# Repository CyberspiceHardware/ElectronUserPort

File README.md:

# Acorn Electron User Port Cartridge 

This is a BBC micro compatible user port cartridge which can be configured
to sit at any of the 16 byte addresses spaces 0xFC80 and above. The standard
address is 0xFCB0.

It also supports a ROM/RAM/FLASH device which can be a 16KB or 32KB part.

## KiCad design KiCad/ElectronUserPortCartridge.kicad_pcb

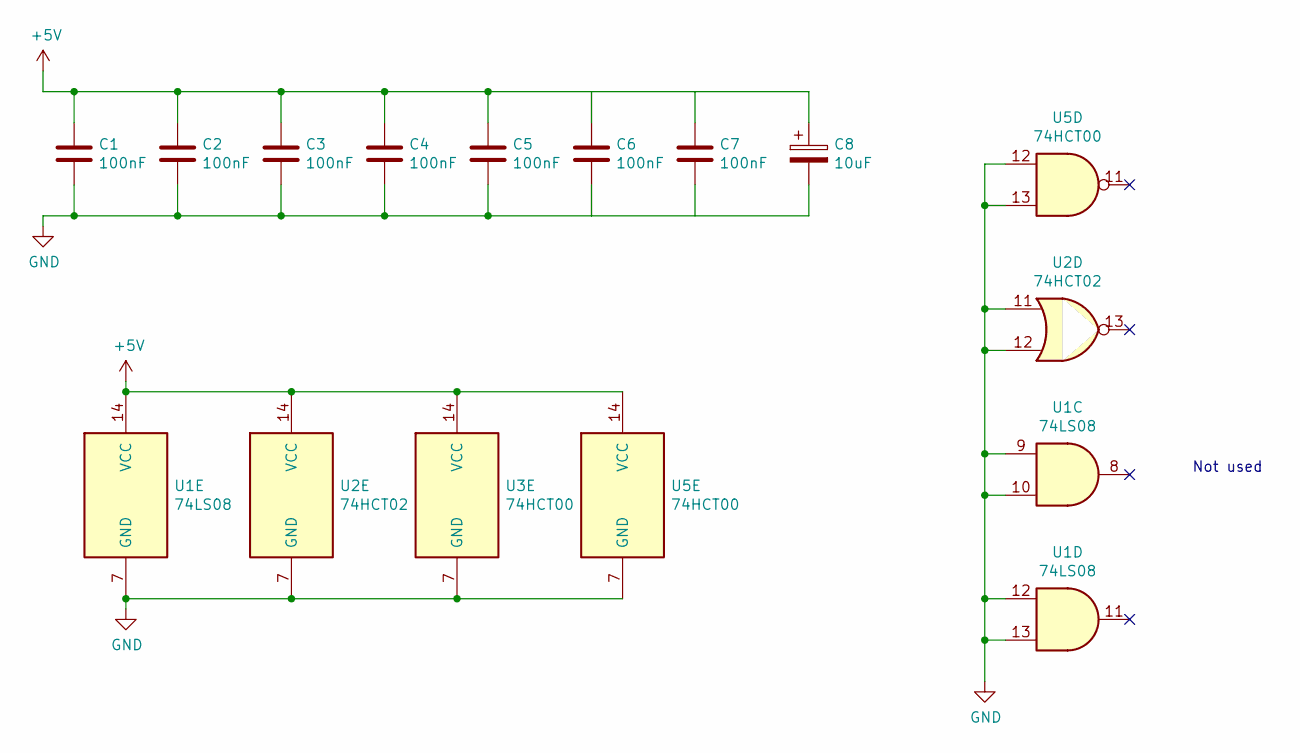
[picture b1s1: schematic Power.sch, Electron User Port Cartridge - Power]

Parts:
C1, C2, C3, C4, C5, C6, C7: 100nF; C_Disc_D7.5mm_W2.5mm_P5.00mm
C8: 10uF; CP_Radial_D5.0mm_P2.50mm
U1: 74LS08
U2: 74HCT02
U3: 74HCT00
U5: 74HCT00; DIP-14_W7.62mm_Socket

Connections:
+5V: C1.1, C2.1, C3.1, C4.1, C5.1, C6.1, C7.1, C8.1, U1.14 (VCC), U2.14 (VCC), U3.14 (VCC), U5.14 (VCC); also elsewhere on the board
GND: C1.2, C2.2, C3.2, C4.2, C5.2, C6.2, C7.2, C8.2, U1.7 (GND), U1.9, U1.10, U1.12, U1.13, U2.7 (GND), U2.11, U2.12, U3.7 (GND), U5.7 (GND), U5.12, U5.13; also elsewhere on the board

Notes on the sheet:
Not used

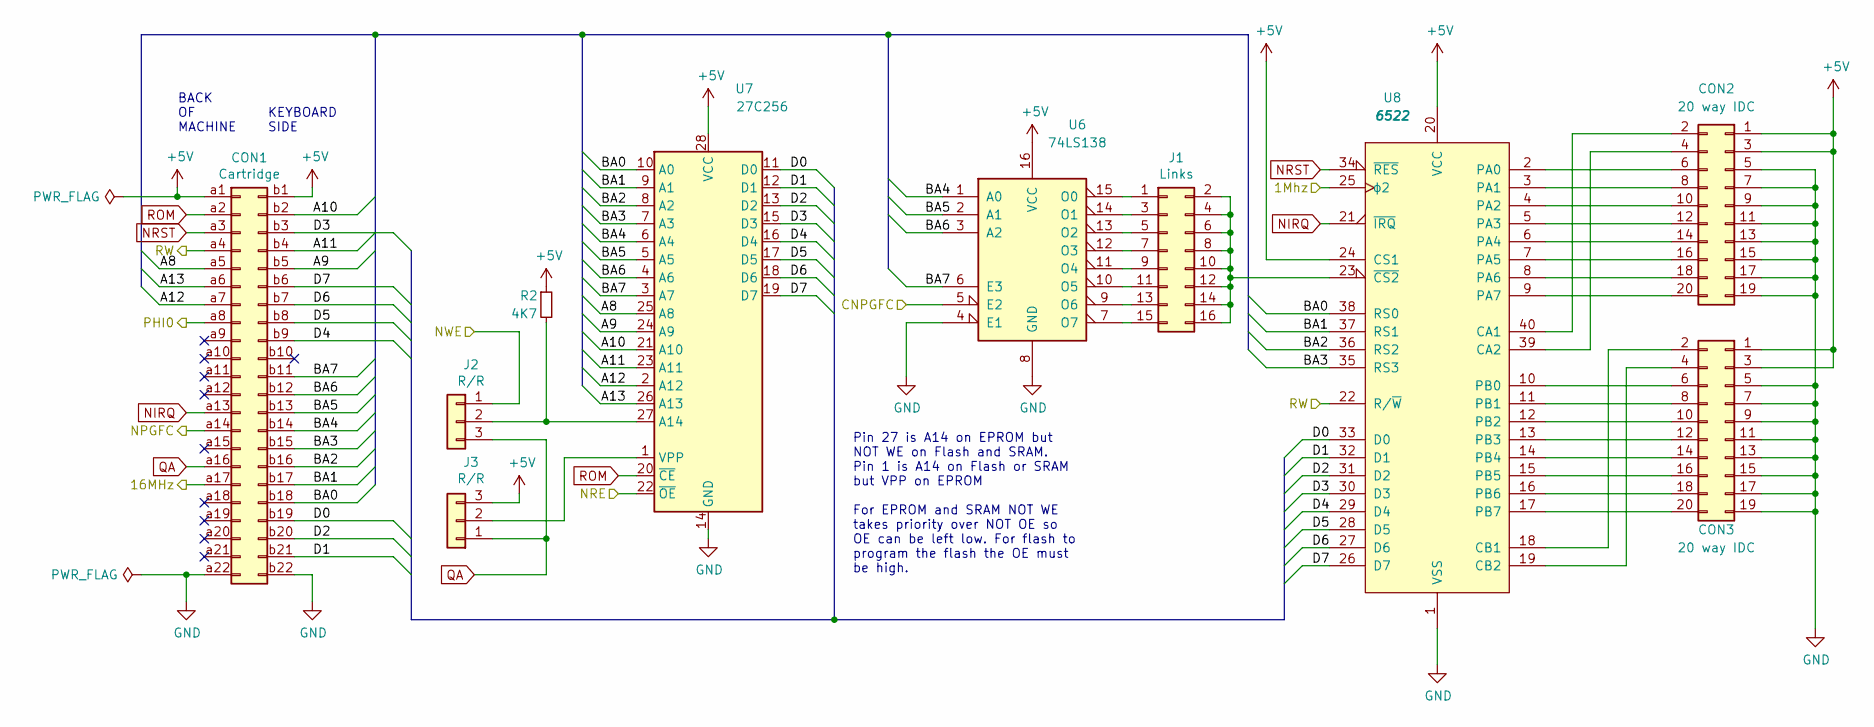
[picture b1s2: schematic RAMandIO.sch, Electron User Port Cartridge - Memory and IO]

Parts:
CON1: Cartridge; ElectronCartridgeEdge
CON2, CON3: 20 way IDC; IDC-Header_2x10-1MP_P2.54mm_Latch_Horizontal
J1: Links; PinHeader_2x08_P2.54mm_Vertical
J2, J3: R/R; PinHeader_1x03_P2.54mm_Vertical
R2: 4K7; R_Axial_DIN0207_L6.3mm_D2.5mm_P7.62mm_Horizontal
U6: 74LS138; DIP-16_W7.62mm_Socket
U7: 27C256; DIP-28_W15.24mm_Socket
U8: 6522; DIP-40_W15.24mm_Socket

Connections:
+5V: CON1.a1, CON1.b1, CON2.1, CON2.3, CON3.1, CON3.3, J3.3, R2.1, U6.16 (VCC), U7.28 (VCC), U8.20 (VCC), U8.24 (CS1); also elsewhere on the board
/ClocksAndSignals/1Mhz: U8.25 (ϕ2); also elsewhere on the board
/ClocksAndSignals/CNPGFC: U6.5 (E2); also elsewhere on the board
/ClocksAndSignals/NPGFC: CON1.a14; also elsewhere on the board
/ClocksAndSignals/NRE: U7.22 (~OE); also elsewhere on the board
/ClocksAndSignals/NWE: J2.1; also elsewhere on the board
/ClocksAndSignals/PHI0: CON1.a8; also elsewhere on the board
/ClocksAndSignals/RW: CON1.a4, U8.22 (R/~W); also elsewhere on the board
/RAMandIO/16MHz: CON1.a17; also elsewhere on the board
/RAMandIO/A8: CON1.a5, U7.25 (A8)
/RAMandIO/A9: CON1.b5, U7.24 (A9)
/RAMandIO/A10: CON1.b2, U7.21 (A10)
/RAMandIO/A11: CON1.b4, U7.23 (A11)
/RAMandIO/A12: CON1.a7, U7.2 (A12)
/RAMandIO/A13: CON1.a6, U7.26 (A13)
/RAMandIO/BA0: CON1.b18, U7.10 (A0), U8.38 (RS0)
/RAMandIO/BA1: CON1.b17, U7.9 (A1), U8.37 (RS1)
/RAMandIO/BA2: CON1.b16, U7.8 (A2), U8.36 (RS2)
/RAMandIO/BA3: CON1.b15, U7.7 (A3), U8.35 (RS3)
/RAMandIO/BA4: CON1.b14, U6.1 (A0), U7.6 (A4)
/RAMandIO/BA5: CON1.b13, U6.2 (A1), U7.5 (A5)
/RAMandIO/BA6: CON1.b12, U6.3 (A2), U7.4 (A6)
/RAMandIO/BA7: CON1.b11, U6.6 (E3), U7.3 (A7)
/RAMandIO/D0: CON1.b19, U7.11 (D0), U8.33 (D0)
/RAMandIO/D1: CON1.b21, U7.12 (D1), U8.32 (D1)
/RAMandIO/D2: CON1.b20, U7.13 (D2), U8.31 (D2)
/RAMandIO/D3: CON1.b3, U7.15 (D3), U8.30 (D3)
/RAMandIO/D4: CON1.b9, U7.16 (D4), U8.29 (D4)
/RAMandIO/D5: CON1.b8, U7.17 (D5), U8.28 (D5)
/RAMandIO/D6: CON1.b7, U7.18 (D6), U8.27 (D6)
/RAMandIO/D7: CON1.b6, U7.19 (D7), U8.26 (D7)
GND: CON1.a22, CON1.b22, CON2.5, CON2.7, CON2.9, CON2.11, CON2.13, CON2.15, CON2.17, CON2.19, CON3.5, CON3.7, CON3.9, CON3.11, CON3.13, CON3.15, CON3.17, CON3.19, U6.4 (E1), U6.8 (GND), U7.14 (GND), U8.1 (VSS); also elsewhere on the board
NIRQ: CON1.a13, U8.21 (~IRQ)
NRST: CON1.a3, U8.34 (~RES)
unnamed: CON2.2, U8.40 (CA1)
unnamed: CON2.4, U8.39 (CA2)
unnamed: CON2.6, U8.2 (PA0)
unnamed: CON2.8, U8.3 (PA1)
unnamed: CON2.10, U8.4 (PA2)
unnamed: CON2.12, U8.5 (PA3)
unnamed: CON2.14, U8.6 (PA4)
unnamed: CON2.16, U8.7 (PA5)
unnamed: CON2.18, U8.8 (PA6)
unnamed: CON2.20, U8.9 (PA7)
unnamed: CON3.2, U8.18 (CB1)
unnamed: CON3.4, U8.19 (CB2)
unnamed: CON3.6, U8.10 (PB0)
unnamed: CON3.8, U8.11 (PB1)
unnamed: CON3.10, U8.12 (PB2)
unnamed: CON3.12, U8.13 (PB3)
unnamed: CON3.14, U8.14 (PB4)
unnamed: CON3.16, U8.15 (PB5)
unnamed: CON3.18, U8.16 (PB6)
unnamed: CON3.20, U8.17 (PB7)
unnamed: J1.1, U6.15 (O0)
unnamed: J1.3, U6.14 (O1)
unnamed: J1.5, U6.13 (O2)
unnamed: J1.7, U6.12 (O3)
unnamed: J1.9, U6.11 (O4)
unnamed: J1.2, J1.4, J1.6, J1.8, J1.10, J1.12, J1.14, J1.16, U8.23 (~CS2)
unnamed: J1.11, U6.10 (O5)
unnamed: J1.13, U6.9 (O6)
unnamed: J1.15, U6.7 (O7)
unnamed: J2.2, R2.2, U7.27 (A14)
unnamed: J3.2, U7.1 (VPP)
QA: CON1.a16, J2.3, J3.1
ROM: CON1.a2, U7.20 (~CE)

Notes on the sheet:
BACK OF MACHINE
KEYBOARD SIDE
Pin 27 is A14 on EPROM but NOT WE on Flash and SRAM. Pin 1 is A14 on Flash or SRAM but VPP on EPROM For EPROM and SRAM NOT WE takes priority over NOT OE so OE can be left low. For flash to program the flash the OE must be high.

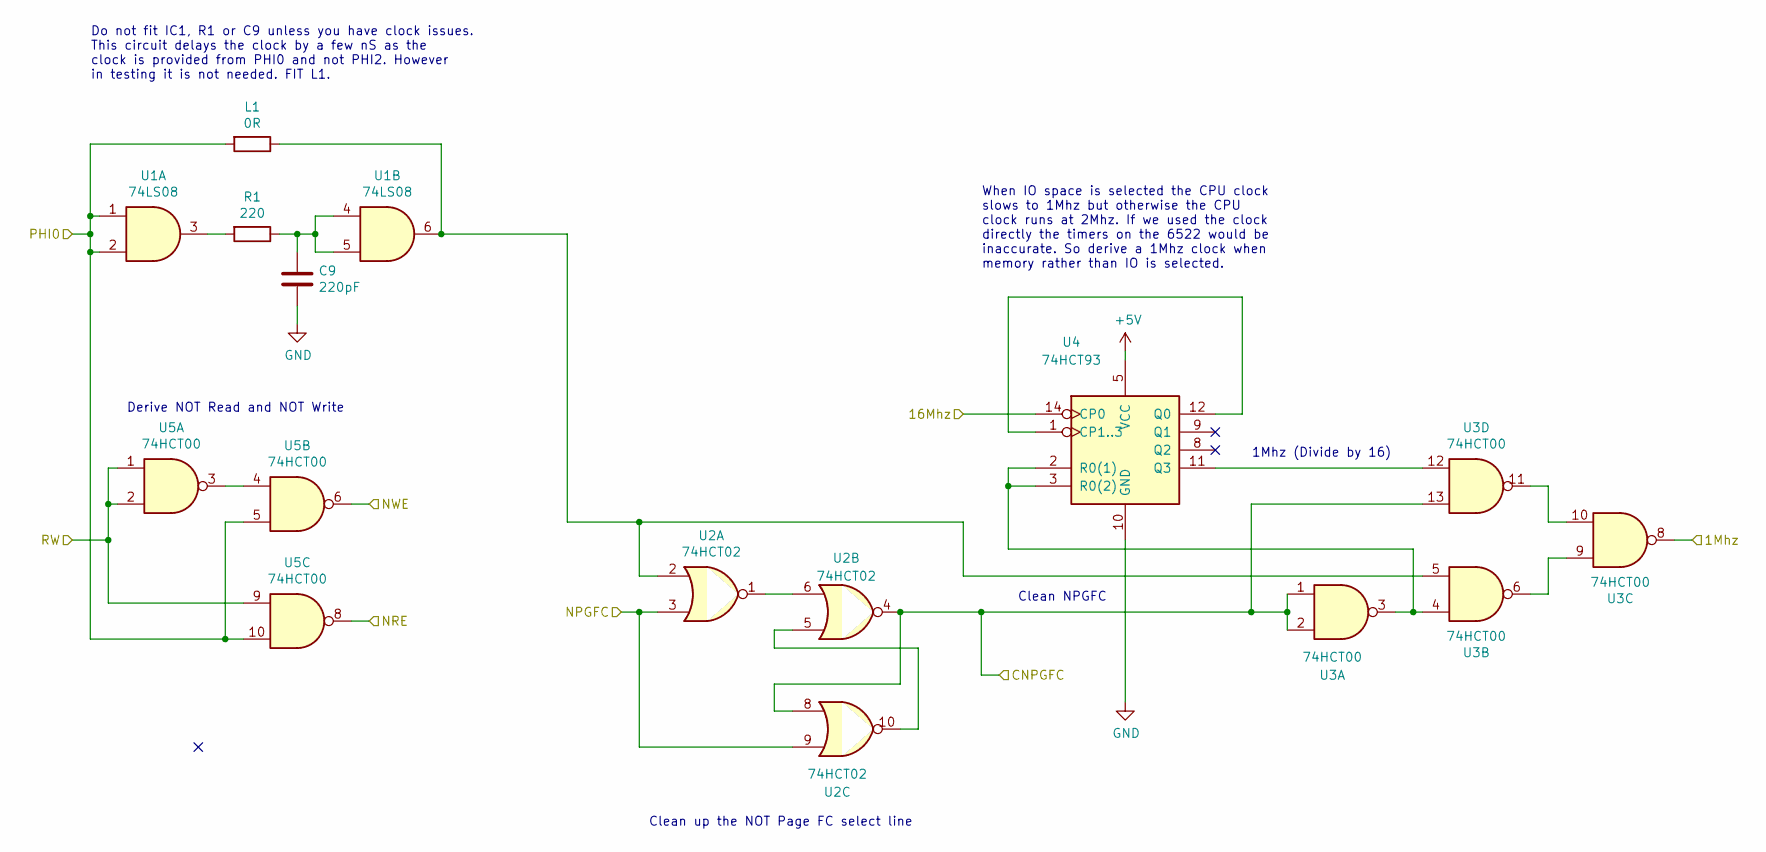
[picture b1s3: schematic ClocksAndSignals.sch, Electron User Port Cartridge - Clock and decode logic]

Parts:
C9: 220pF; C_Disc_D7.0mm_W2.5mm_P5.00mm
L1: 0R; R_Axial_DIN0204_L3.6mm_D1.6mm_P7.62mm_Horizontal
R1: 220; R_Axial_DIN0207_L6.3mm_D2.5mm_P7.62mm_Horizontal
U1: 74LS08; DIP-14_W7.62mm_Socket
U2: 74HCT02; DIP-14_W7.62mm_Socket
U3, U5: 74HCT00; DIP-14_W7.62mm_Socket
U4: 74HCT93; DIP-14_W7.62mm_Socket

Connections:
+5V: U4.5 (VCC); also elsewhere on the board
/ClocksAndSignals/1Mhz: U3.8; also elsewhere on the board
/ClocksAndSignals/CNPGFC: U2.4, U2.8, U3.1, U3.2, U3.13; also elsewhere on the board
/ClocksAndSignals/NPGFC: U2.3, U2.9; also elsewhere on the board
/ClocksAndSignals/NRE: U5.8; also elsewhere on the board
/ClocksAndSignals/NWE: U5.6; also elsewhere on the board
/ClocksAndSignals/PHI0: L1.2, U1.1, U1.2, U5.5, U5.10; also elsewhere on the board
/ClocksAndSignals/RW: U5.1, U5.2, U5.9; also elsewhere on the board
/RAMandIO/16MHz: U4.14 (CP0); also elsewhere on the board
GND: C9.2, U4.10 (GND); also elsewhere on the board
unnamed: C9.1, R1.1, U1.4, U1.5
unnamed: L1.1, U1.6, U2.2, U3.5
unnamed: R1.2, U1.3
unnamed: U2.1, U2.6
unnamed: U2.5, U2.10
unnamed: U3.3, U3.4, U4.2 (R0(1)), U4.3 (R0(2))
unnamed: U3.6, U3.9
unnamed: U3.10, U3.11
unnamed: U3.12, U4.11 (Q3)
unnamed: U4.1 (CP1..3), U4.12 (Q0)
unnamed: U5.3, U5.4

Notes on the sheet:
1Mhz (Divide by 16)
Clean NPGFC
Clean up the NOT Page FC select line
Derive NOT Read and NOT Write
When IO space is selected the CPU clock slows to 1Mhz but otherwise the CPU clock runs at 2Mhz. If we used the clock directly the timers on the 6522 would be inaccurate. So derive a 1Mhz clock when memory rather than IO is selected.
Do not fit IC1, R1 or C9 unless you have clock issues. This circuit delays the clock by a few nS as the clock is provided from PHI0 and not PHI2. However in testing it is not needed. FIT L1.

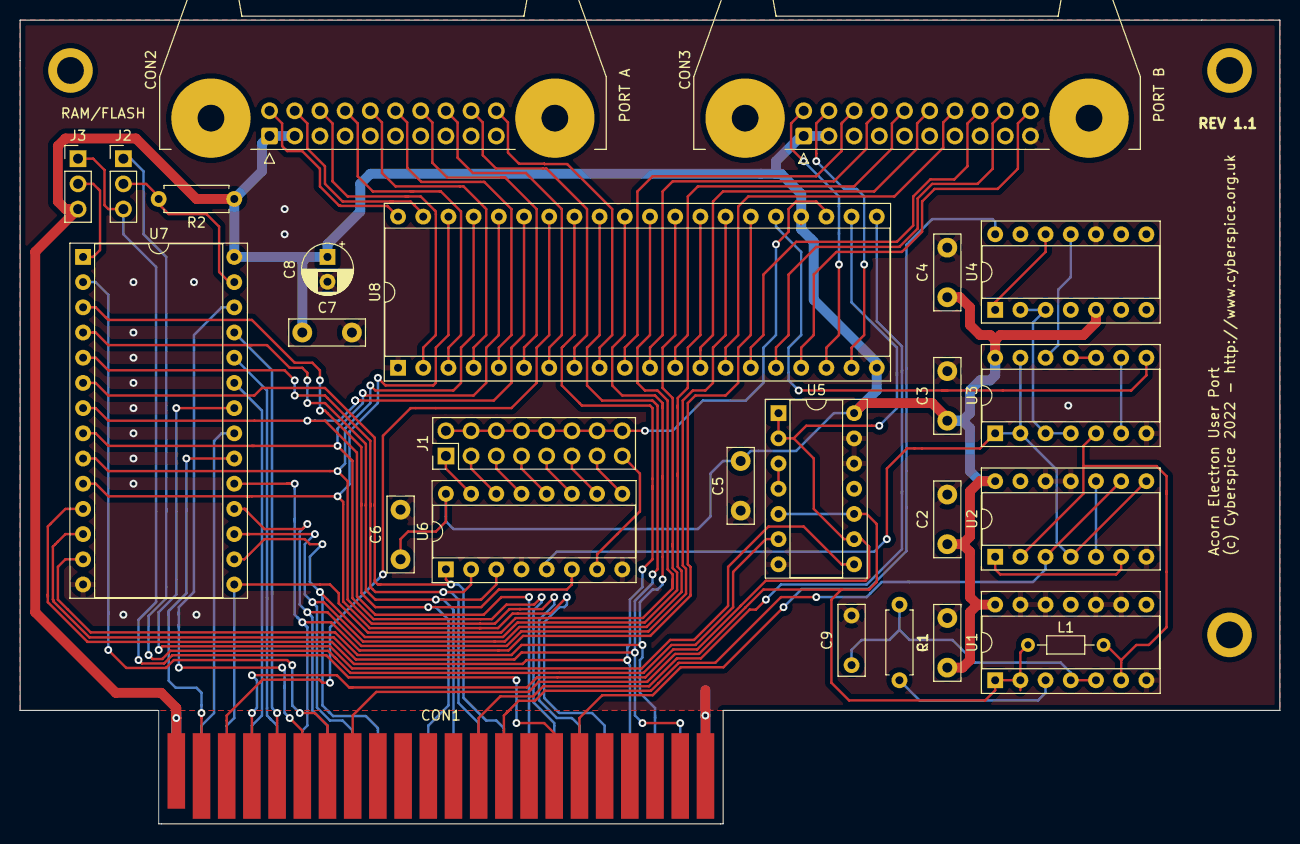
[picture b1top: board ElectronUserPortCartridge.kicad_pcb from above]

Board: 2 copper layers, 127.0 x 81.0 mm, 29 parts (0 on the bottom side), 78 nets.

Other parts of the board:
hole1, hole2, hole3: MountingHole_2.7mm_M2.5_ISO7380_Pad

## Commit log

2022-03-01 Added schematic as a PDF and gerber files
2022-06-01 Updates for fixes (Rev A2)
